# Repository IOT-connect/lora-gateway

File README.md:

# Lora gateway with ethernet

## Project for make simple and reliable Lora gateway with AVR atmega2560 and ESR-US1 w5500 ethernet

#### 3d view

#### pcb view

#### schematic view

### TODO

- [ ] Add RTC
- [ ] Add temperature sensor

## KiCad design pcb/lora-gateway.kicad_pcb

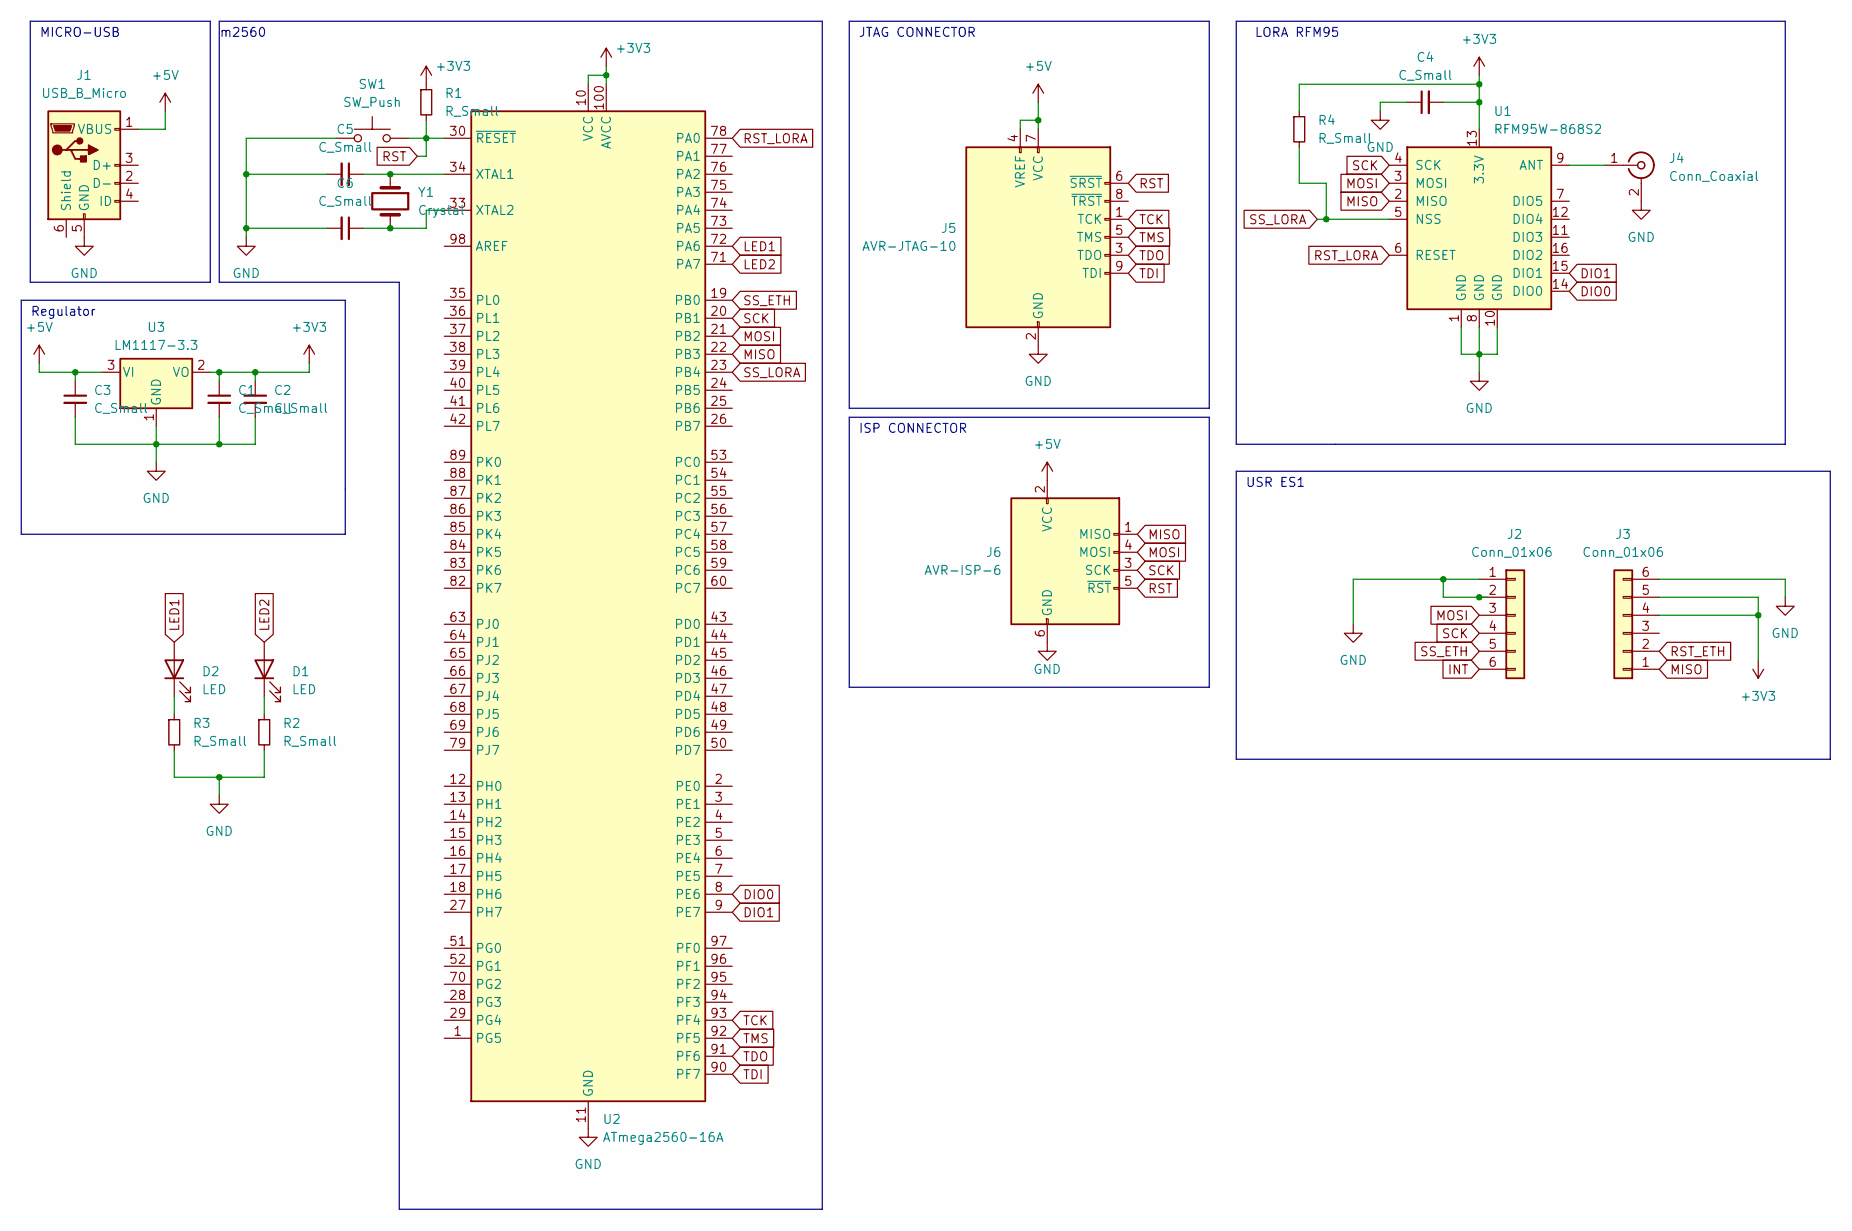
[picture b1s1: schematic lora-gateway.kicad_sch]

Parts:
C1, C2, C3, C4, C5, C6: C_Small; C_0603_1608Metric
D1, D2: LED; LED_0603_1608Metric
J1: USB_B_Micro; USB_Micro-B_Amphenol_10103594-0001LF_Horizontal
J2, J3: Conn_01x06; PinHeader_1x06_P2.54mm_Vertical
J4: Conn_Coaxial; SMA_Molex_73251-2120_EdgeMount_Horizontal
J5: AVR-JTAG-10; PinHeader_2x05_P2.54mm_Vertical
J6: AVR-ISP-6; PinHeader_2x03_P2.54mm_Vertical
R1, R2, R3, R4: R_Small; R_0603_1608Metric
SW1: SW_Push; SW_SPST_CK_RS282G05A3
U1: RFM95W-868S2; HOPERF_RFM9XW_SMD
U2: ATmega2560-16A; TQFP-100_14x14mm_P0.5mm
U3: LM1117-3.3; SOT-223-3_TabPin2
Y1: Crystal; Crystal_SMD_5032-2Pin_5.0x3.2mm

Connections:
+3V3: C1.1, C2.1, C4.2, J3.4, J3.5, R1.1, R4.1, U1.13 (3.3V), U2.10 (VCC), U2.31 (VCC), U2.61 (VCC), U2.80 (VCC), U2.100 (AVCC), U3.2 (VO)
+5V: C3.1, J1.1 (VBUS), J5.4 (VREF), J5.7 (VCC), J6.2 (VCC), U3.3 (VI)
DIO0: U1.14 (DIO0), U2.8 (PE6)
DIO1: U1.15 (DIO1), U2.9 (PE7)
GND: C1.2, C2.2, C3.2, C4.1, C5.2, C6.2, J1.5 (GND), J2.1, J2.2, J3.6, J4.2 (Ext), J5.2 (GND), J5.10 (GND), J6.6 (GND), R2.2, R3.2, SW1.1, U1.1 (GND), U1.8 (GND), U1.10 (GND), U2.11 (GND), U2.32 (GND), U2.62 (GND), U2.81 (GND), U2.99 (GND), U3.1 (GND)
INT: J2.6
LED1: D2.2 (A), U2.72 (PA6)
LED2: D1.2 (A), U2.71 (PA7)
MISO: J3.1, J6.1 (MISO), U1.2 (MISO), U2.22 (PB3)
MOSI: J2.3, J6.4 (MOSI), U1.3 (MOSI), U2.21 (PB2)
unnamed: D1.1 (K), R2.1
unnamed: D2.1 (K), R3.1
unnamed: J4.1 (In), U1.9 (ANT)
unnamed: C5.1, U2.34 (XTAL1), Y1.1
unnamed: C6.1, U2.33 (XTAL2), Y1.2
RST: J5.6 (~SRST), J6.5 (~RST), R1.2, SW1.2, U2.30 (~RESET)
RST_ETH: J3.2
RST_LORA: U1.6 (RESET), U2.78 (PA0)
SCK: J2.4, J6.3 (SCK), U1.4 (SCK), U2.20 (PB1)
SS_ETH: J2.5, U2.19 (PB0)
SS_LORA: R4.2, U1.5 (NSS), U2.23 (PB4)
TCK: J5.1 (TCK), U2.93 (PF4)
TDI: J5.9 (TDI), U2.90 (PF7)
TDO: J5.3 (TDO), U2.91 (PF6)
TMS: J5.5 (TMS), U2.92 (PF5)

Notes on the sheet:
USR ES1
Regulator
ISP CONNECTOR
MICRO-USB
m2560
LORA RFM95
JTAG CONNECTOR

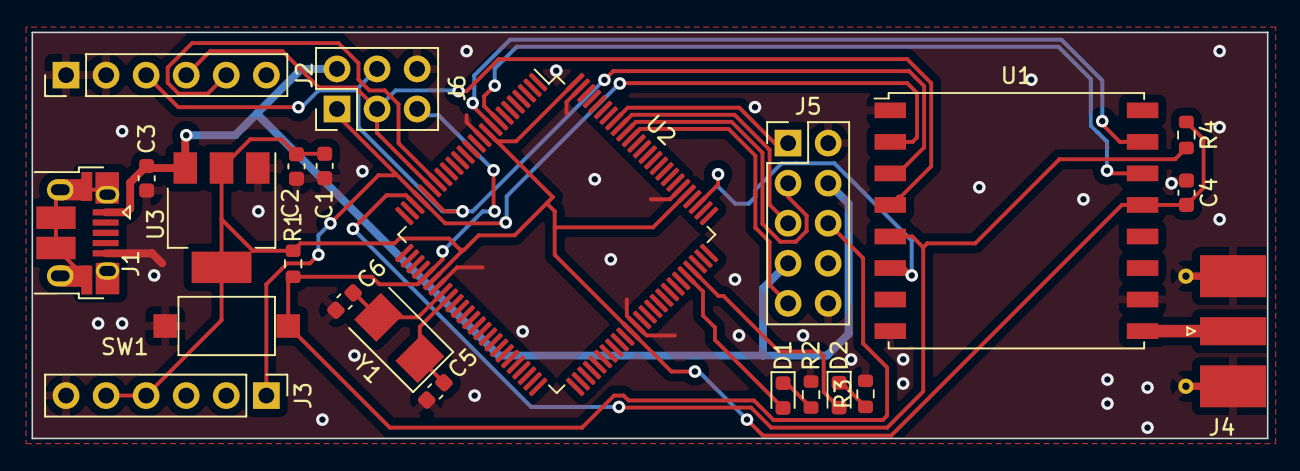
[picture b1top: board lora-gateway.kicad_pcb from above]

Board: 2 copper layers, 78.3 x 25.8 mm, 23 parts (0 on the bottom side), 23 nets.

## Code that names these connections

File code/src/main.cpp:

#include <Arduino.h>
#include <SPI.h>
#include <Ethernet3.h>
#include <EthernetUdp3.h>
#include <RadioLib.h>

#include <SoftwareSerial.h>

#define LED1 PIN_PA6
#define LED2 PIN_PA7

SoftwareSerial Serial5(A5,A6);

byte mac[] = {
  0xDE, 0xAD, 0xBE, 0xEF, 0xFE, 0xED
};

unsigned int localPort = 1883;    //10002;  // local port to listen on

char packetBuffer[UDP_TX_PACKET_MAX_SIZE]; //buffer to hold incoming packet,
char ReplyBuffer[] = "acknowledged";       // a string to send back

EthernetUDP Udp;
RFM95 radio = new Module(19, 0, 0, 0);

void setup() {
  pinMode(LED1, OUTPUT);
  Serial5.begin(9600);
  delay(2000);
  Ethernet.setCsPin(PIN_PB0);
  Ethernet.begin(mac);

  Udp.begin(2000);

  Serial.print(F("[SX1278] Initializing ... "));
  int state = radio.begin(868.0);
  if (state == RADIOLIB_ERR_NONE) {
    Serial5.println(F("success!"));
  } else {
    Serial5.print(F("failed, code "));
    Serial5.println(state);
    while (true);
  }



  Serial5.println(Ethernet.localIP());
}

void loop() {
  int packetSize = Udp.parsePacket();
  if (packetSize)
  {
    Serial5.print("Received packet of size ");
    Serial5.println(packetSize);
    Serial5.print("From ");
    IPAddress remote = Udp.remoteIP();
    for (int i = 0; i < 4; i++)
    {
      Serial5.print(remote[i], DEC);
      if (i < 3)
      {
        Serial5.print(".");
      }
    }
    Serial5.print(", port ");
    Serial5.println(Udp.remotePort());

    Udp.read(packetBuffer, UDP_TX_PACKET_MAX_SIZE);
    Serial5.println("Contents:");
    Serial5.println(packetBuffer);

    // send a reply, to the IP address and port that sent us the packet we received
    Udp.beginPacket(Udp.remoteIP(), Udp.remotePort());
    Udp.write(ReplyBuffer);
    Udp.endPacket();
  }
  delay(10);
}

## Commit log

2023-07-10 add m2560 + rfm95
2023-07-11 add board + usr es1 connector
2023-07-11 add regulator
2023-07-14 add isp + jtag connector
2023-07-14 pcb wiring
2023-07-14 add pictures
2023-07-14 add readme
2023-07-14 up readme
2023-07-14 up schematic
2023-07-14 up pcb
2023-07-14 up 3d view with sma + rfm95
2023-07-14 update alt readme
2023-07-14 update todo readme
2023-07-26 add leds
2023-07-27 first lora gateway code
2023-07-28 add ethernet lib + code
2023-07-29 add dhcp
2023-07-29 add lora
2023-07-29 add rfm95 wiring
2023-07-30 add gnd to micro usb
2023-07-30 add project file
2023-07-30 add eslint
2023-07-30 transfert server file
2023-08-12 add led pin
2023-08-12 add usb gnd
2023-09-01 change DIO0 & DIO1 to interrupt pin
2023-09-01 add lora lib
